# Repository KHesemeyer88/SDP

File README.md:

# SDP
Everyone has their own branch. 
You only work in your own branch.
Main only gets updated once a week and requires approval.
To collaborate in between, merge with your collaborator's branch back and forth.
To change branches: git checkout main, git checkout origin/YourBranch, etc.
To merge changes your collaborator made: git merge origin/CollaboratorBranch, etc.
  -Then resolve any merge conflicts, sync changes.

To get yourself up to date with main:
  -git checkout main
  -git pull
  -git checkout origin/YourBranch
  -git merge main

To merge person A to person B
-person A has updates / new code

In old/out_of_date branch

git merge the_branch_with_updates

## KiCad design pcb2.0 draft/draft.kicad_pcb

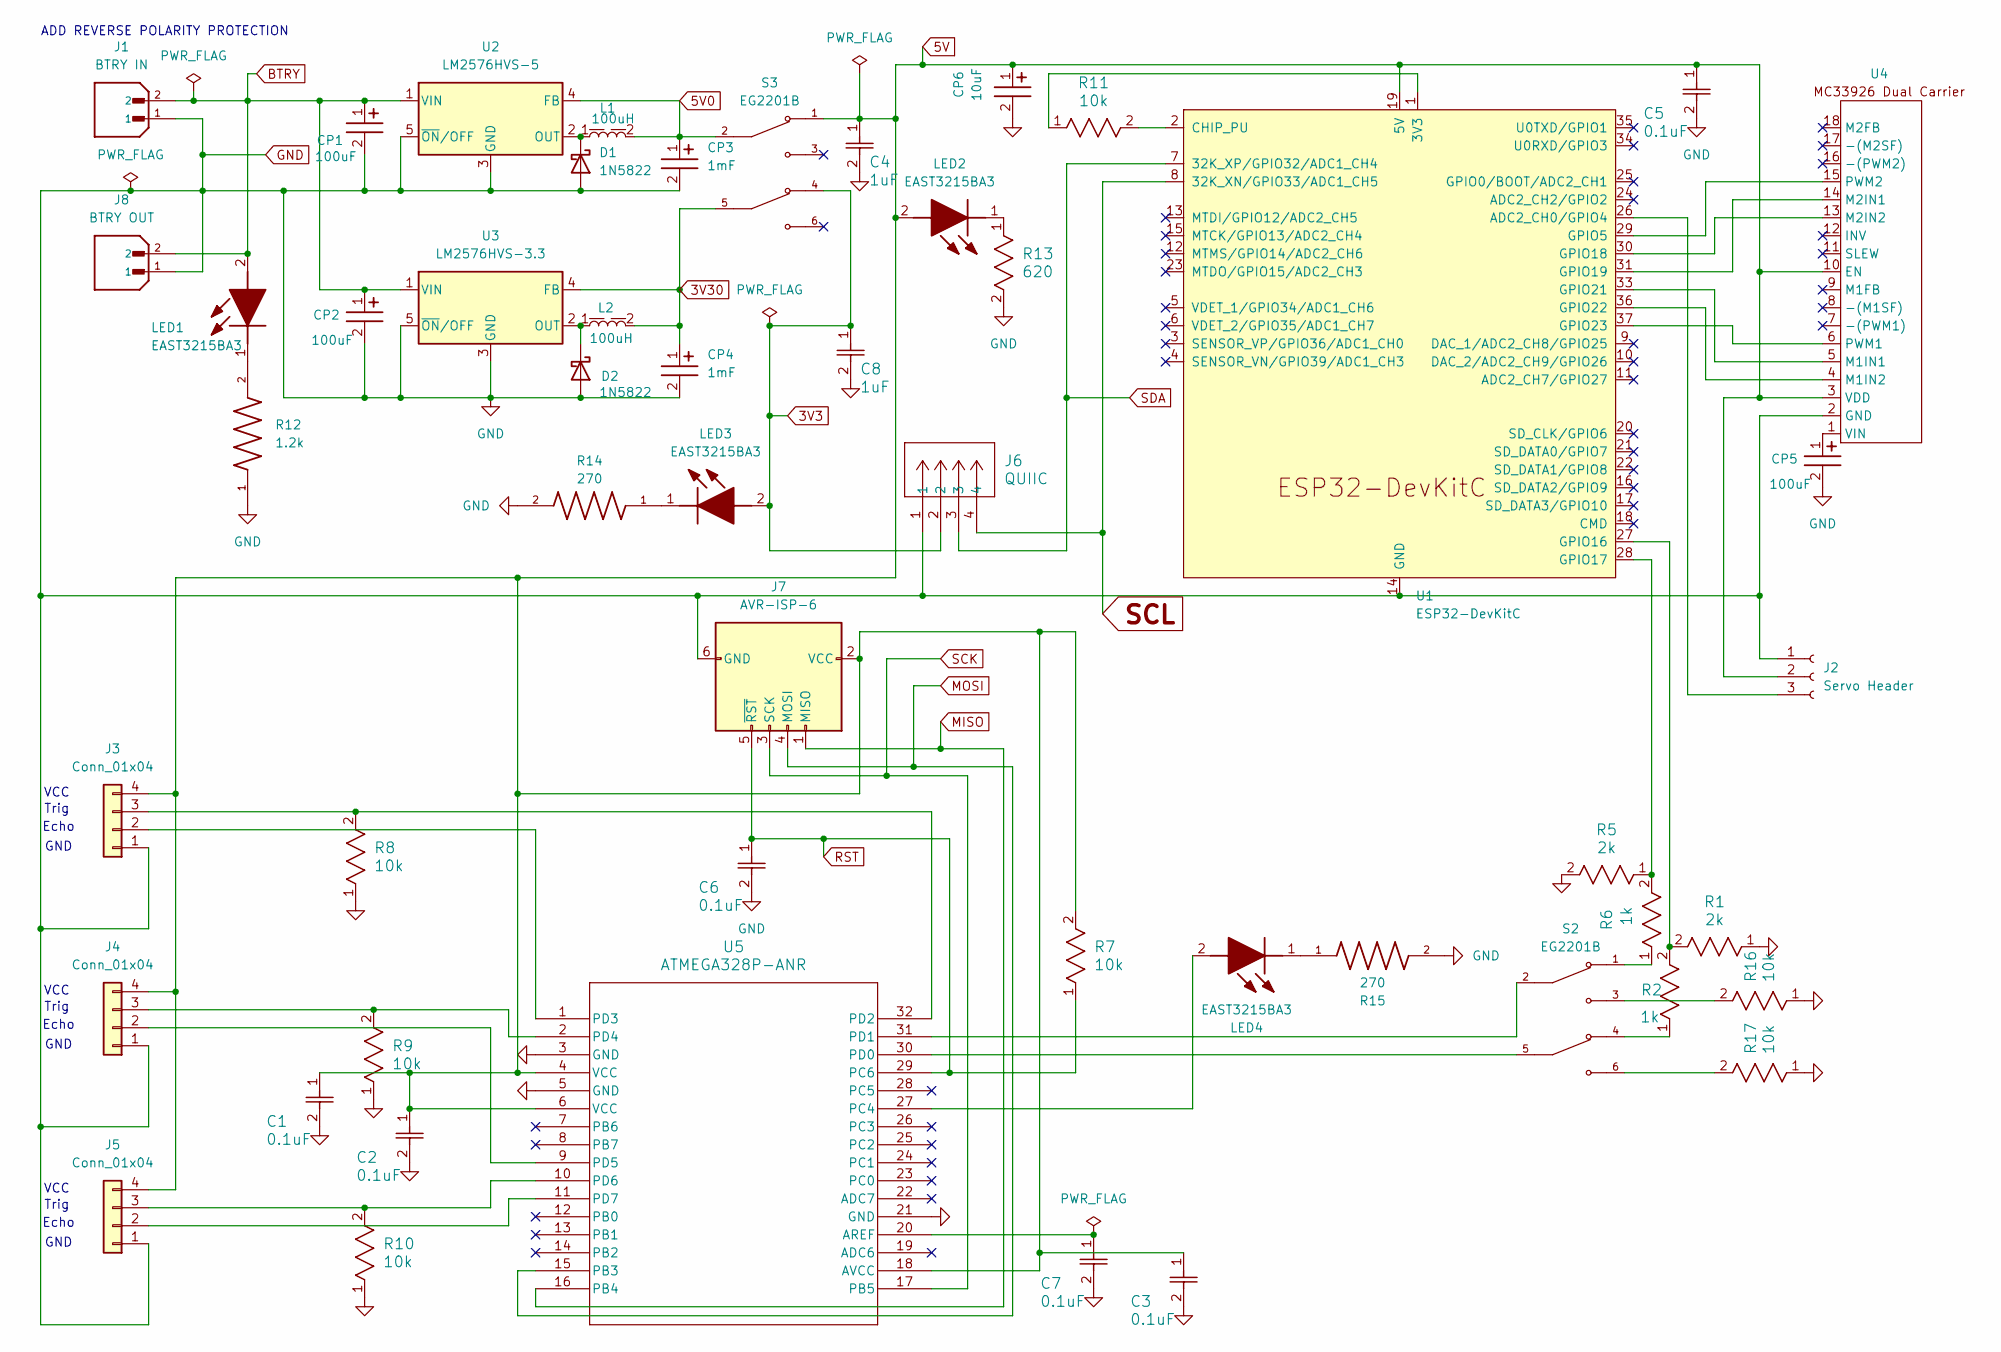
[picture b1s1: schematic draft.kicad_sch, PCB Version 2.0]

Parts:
C1, C2, C3, C5, C6, C7: 0.1uF; G-188_MUR-L
C4, C8: 1uF; CAP_GRM21_MUR-L
CP1, CP2, CP5: 100uF; CP_Wurth_WCAP-PSLP-D5L5.5; Part Number 875105242010
CP3, CP4: 1mF; CP_Wurth_WCAP-ASLI-D12.5L14; Part Number 865080462016
CP6: 10uF; CP_Wurth_WCAP-PSLP-D5L5.8; Part Number 875105359001
D1, D2: 1N5822; D_DO-201AD_P15.24mm_Horizontal
J1: BTRY IN; JST_B2B-XH-A; PARTREV N/A
J2: Servo Header; PinSocket_1x03_P2.54mm_Vertical
J3, J4, J5: Conn_01x04; PinHeader_1x04_P2.54mm_Vertical
J6: QUIIC; CONN_SM04B-SRSS-TB_JST
J7: AVR-ISP-6; IDC-Header_2x03_P2.54mm_Vertical
J8: BTRY OUT; JST_B2B-XH-A; PARTREV N/A
L1, L2: 100uH; L_Wurth_WE-PD-1245; Part Number 7447715101
LED1, LED2, LED3, LED4: EAST3215BA3; LEDC3215X110N; Mouser Part Number 638-EAST3215BA3
R1, R5: 2k; RES_CR0805_VEN-L
R2, R6: 1k; RES_CR0805_VEN-L
R7, R8, R9, R10, R11, R16, R17: 10k; RES_CR0805_VEN-L
R12: 1.2k; RES_ERJU08J122V; PARTREV 3/1/2020
R13: 620; RC1206N_PAN-L
R14, R15: 270; RES_ERJU08J271V; PARTREV 3/1/2020
S2, S3: EG2201B; SW_EG2201B; PARTREV C
U1: ESP32-DevKitC
U2: LM2576HVS-5; TO-263-5_TabPin3
U3: LM2576HVS-3.3; TO-263-5_TabPin3
U4: polulu_MC33926_dual
U5: ATMEGA328P-ANR; 32A_ATM-L

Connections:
3V3: C8.1, J6.2, LED3.2 (A), S3.4
3V30: CP4.1, L2.2, S3.5, U3.4 (FB)
5V: C1.1, C2.1, C3.1, C4.1, C5.1, CP6.1, J2.2, J3.4, J4.4, J5.4, J7.2 (VCC), LED2.2 (A), R7.2, S3.1, U1.19 (5V), U4.3 (VDD), U4.10 (EN), U5.4 (VCC), U5.6 (VCC), U5.18 (AVCC)
5V0: CP3.1, L1.2, S3.2, U2.4 (FB)
BTRY: CP1.1, CP2.1, J1.2, J8.2, LED1.2 (A), U2.1 (VIN), U3.1 (VIN)
GND: C1.2, C2.2, C3.2, C4.2, C5.2, C6.2, C7.2, C8.2, CP1.2, CP2.2, CP3.2, CP4.2, CP5.2, CP6.2, D1.2 (A), D2.2 (A), J1.1, J2.1, J3.1, J4.1, J5.1, J6.1, J7.6 (GND), J8.1, R1.1, R5.2, R8.1, R9.1, R10.1, R12.1, R13.2, R14.2, R15.2, R16.1, R17.1, U1.14 (GND), U1.32 (GND), U1.38 (GND), U2.3 (GND), U2.5 (~ON/OFF), U3.3 (GND), U3.5 (~ON/OFF), U4.2 (GND), U5.3 (GND), U5.5 (GND), U5.21 (GND)
MISO: J7.1 (MISO), U5.16 (PB4)
MOSI: J7.4 (MOSI), U5.15 (PB3)
unnamed: D1.1 (K), L1.1, U2.2 (OUT)
unnamed: D2.1 (K), L2.1, U3.2 (OUT)
unnamed: J2.3, U1.26 (ADC2_CH0/GPIO4)
unnamed: J3.2, U5.1 (PD3)
unnamed: J3.3, R8.2, U5.32 (PD2)
unnamed: J4.2, U5.9 (PD5)
unnamed: J4.3, R9.2, U5.2 (PD4)
unnamed: J5.2, U5.11 (PD7)
unnamed: J5.3, R10.2, U5.10 (PD6)
unnamed: LED1.1 (K), R12.2
unnamed: LED2.1 (K), R13.1
unnamed: LED3.1 (K), R14.1
unnamed: LED4.2 (A), U5.27 (PC4)
unnamed: LED4.1 (K), R15.1
unnamed: R2.1, S2.4
unnamed: R6.1, S2.1
unnamed: R16.2, S2.3
unnamed: R17.2, S2.6
unnamed: R11.1, U1.1 (3V3)
unnamed: R11.2, U1.2 (CHIP_PU)
unnamed: U1.29 (GPIO5), U4.15 (PWM2)
unnamed: R1.2, R2.2, U1.27 (GPIO16)
unnamed: R5.1, R6.2, U1.28 (GPIO17)
unnamed: U1.30 (GPIO18), U4.13 (M2IN2)
unnamed: U1.31 (GPIO19), U4.14 (M2IN1)
unnamed: U1.33 (GPIO21), U4.5 (M1IN1)
unnamed: U1.36 (GPIO22), U4.4 (M1IN2)
unnamed: U1.37 (GPIO23), U4.6 (PWM1)
unnamed: CP5.1, U4.1 (VIN)
unnamed: C7.1, U5.20 (AREF)
unnamed: S2.5, U5.30 (PD0)
unnamed: S2.2, U5.31 (PD1)
RST: C6.1, J7.5 (~RST), R7.1, U5.29 (PC6)
SCK: J7.3 (SCK), U5.17 (PB5)
SCL: J6.4, U1.8 (32K_XN/GPIO33/ADC1_CH5)
SDA: J6.3, U1.7 (32K_XP/GPIO32/ADC1_CH4)

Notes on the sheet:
GND
Echo
VCC
Trig
ADD REVERSE POLARITY PROTECTION

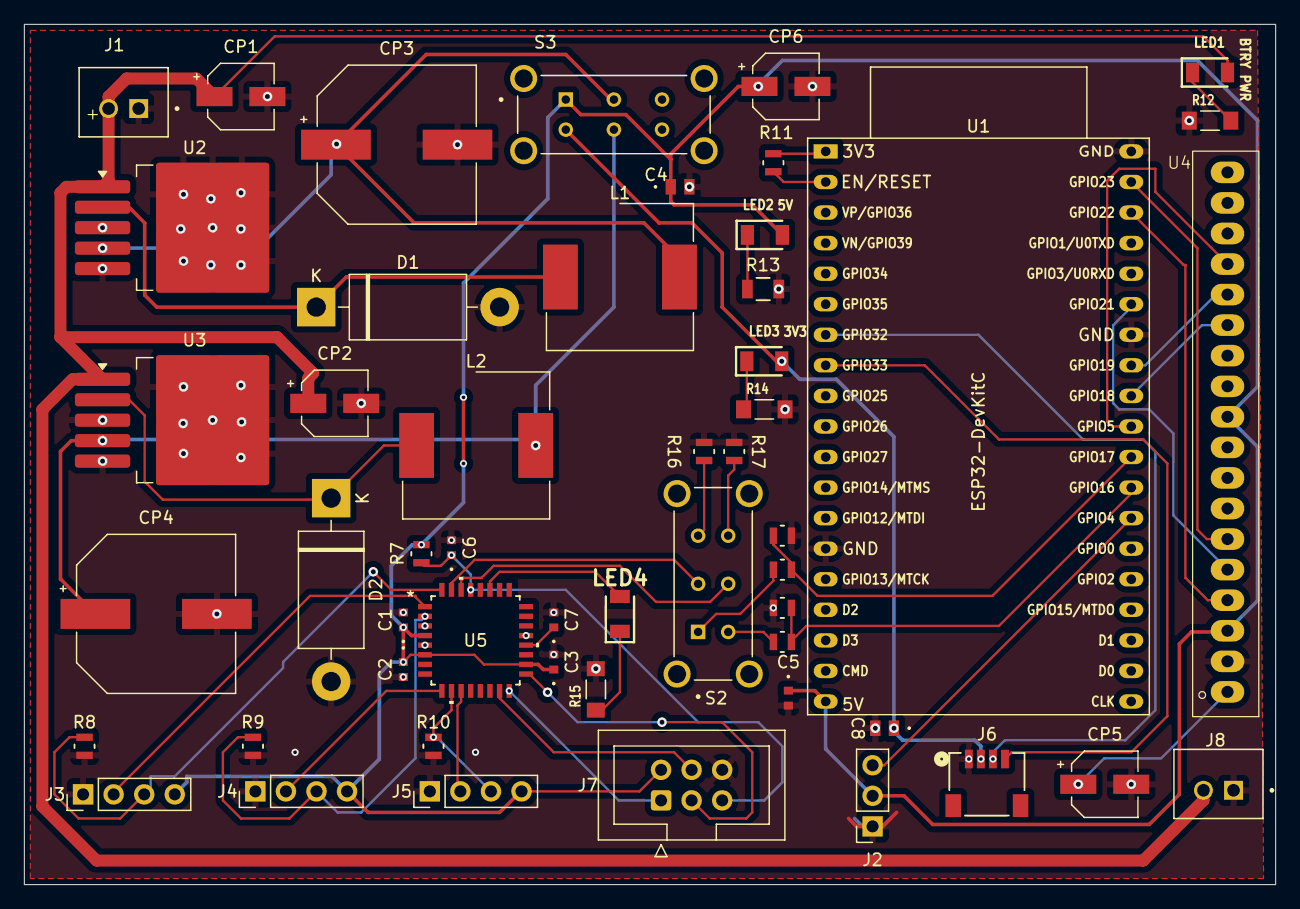
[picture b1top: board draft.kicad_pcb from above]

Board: 2 copper layers, 104.0 x 71.5 mm, 52 parts (0 on the bottom side), 44 nets.

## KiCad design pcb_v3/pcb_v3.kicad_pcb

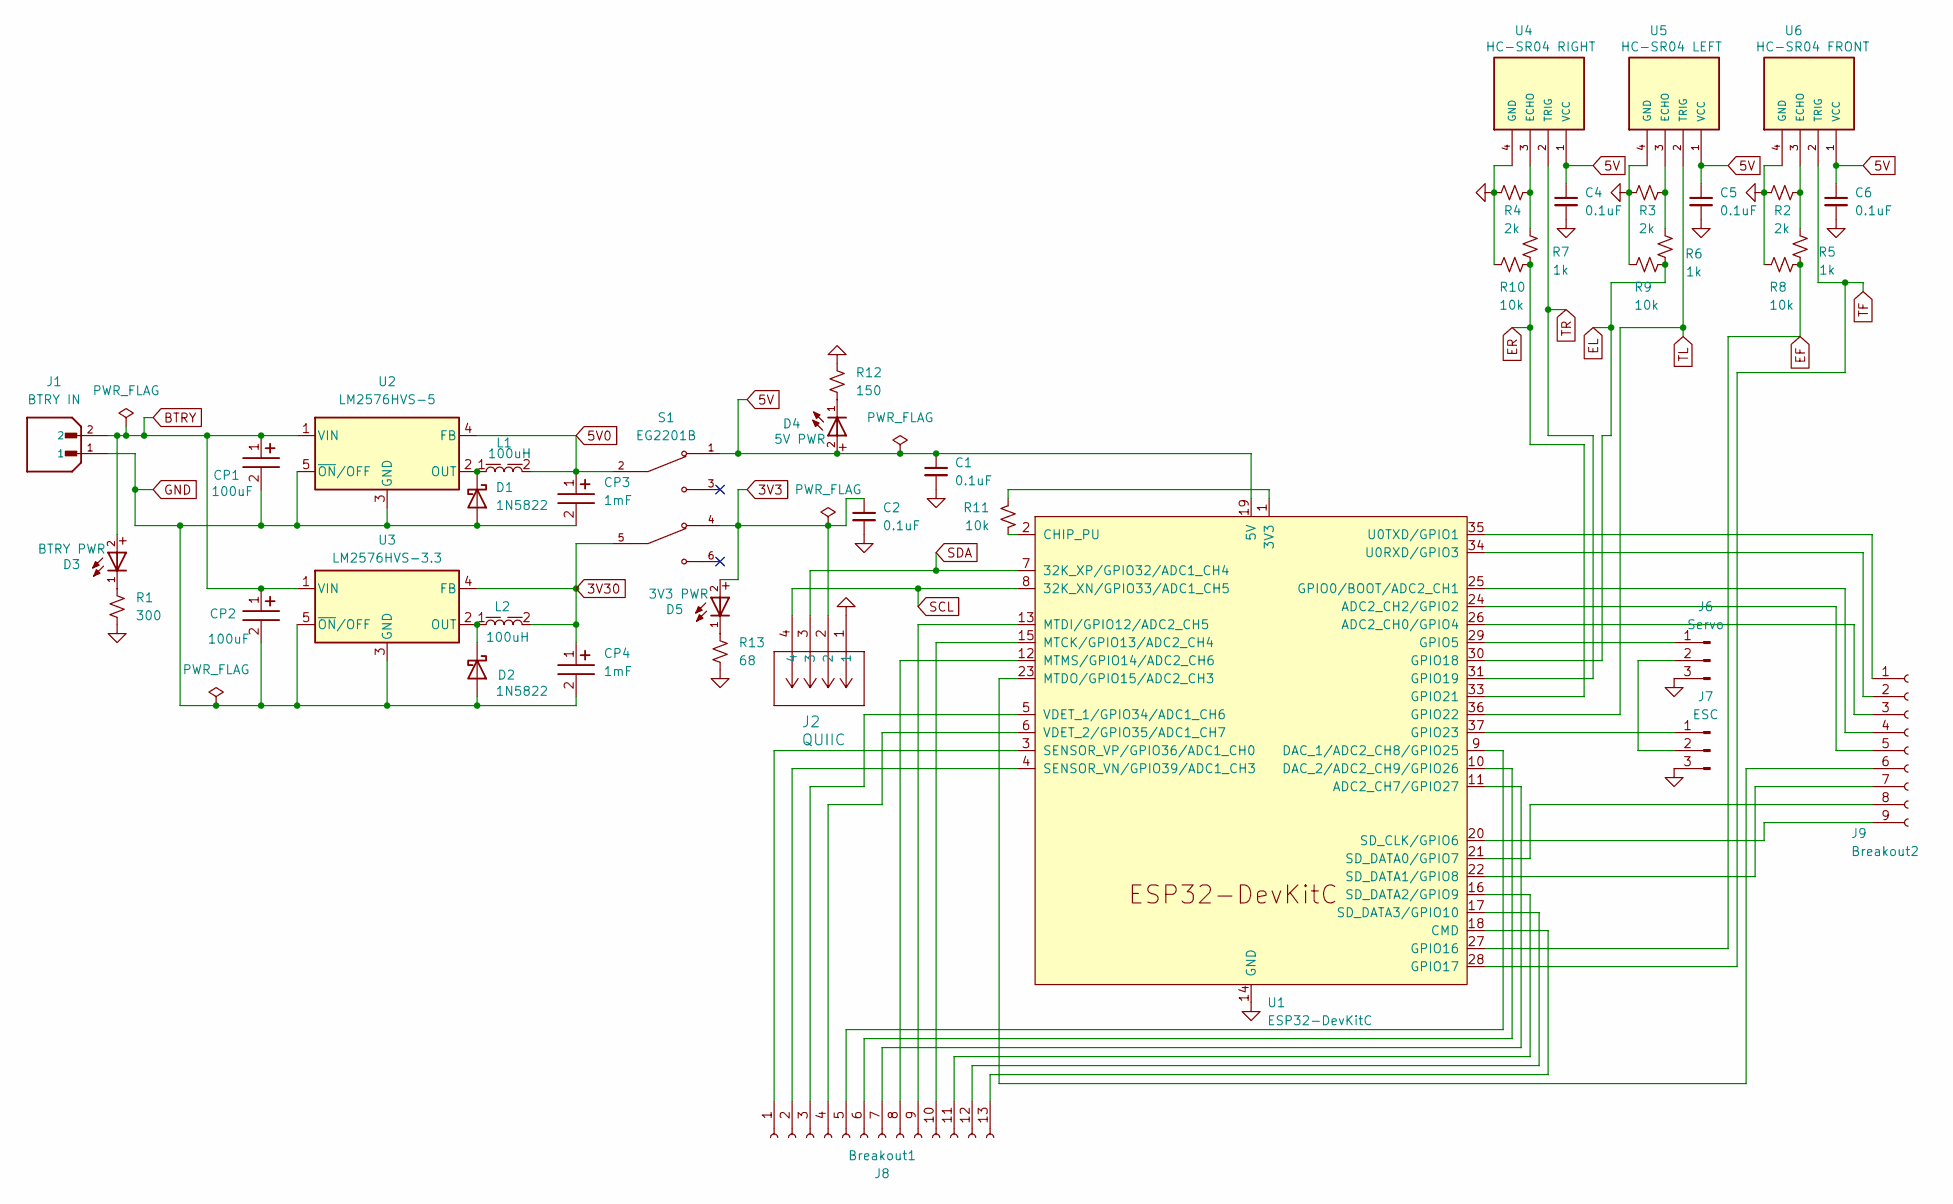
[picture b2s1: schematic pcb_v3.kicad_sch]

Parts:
C1, C2, C4, C5, C6: 0.1uF; C_1206_3216Metric_Pad1.33x1.80mm_HandSolder
CP1, CP2: 100uF; CP_Wurth_WCAP-PSLP-D5L5.5; Part Number 875105242010
CP3, CP4: 1mF; CP_Wurth_WCAP-ASLI-D12.5L14; Part Number 865080462016
D1, D2: 1N5822; D_DO-201AD_P15.24mm_Horizontal
D3: BTRY PWR; WL-SMSW_3014_LED
D4: 5V PWR; WL-SMSW_3014_LED
D5: 3V3 PWR; WL-SMSW_3014_LED
J1: BTRY IN; JST_B2B-XH-A; PARTREV N/A
J2: QUIIC; CONN_SM04B-SRSS-TB_JST
J6: Servo; JST_XH_B3B-XH-A_1x03_P2.50mm_Vertical
J7: ESC; JST_XH_B3B-XH-A_1x03_P2.50mm_Vertical
J8: Breakout1; PinSocket_1x13_P2.54mm_Vertical
J9: Breakout2; PinSocket_1x09_P2.54mm_Vertical
L1, L2: 100uH; L_Wurth_WE-PD-1245; Part Number 7447715101
R1: 300; R_1206_3216Metric_Pad1.30x1.75mm_HandSolder
R2, R3, R4: 2k; R_1206_3216Metric_Pad1.30x1.75mm_HandSolder
R5, R6, R7: 1k; R_1206_3216Metric_Pad1.30x1.75mm_HandSolder
R8, R9, R10, R11: 10k; R_1206_3216Metric_Pad1.30x1.75mm_HandSolder
R12: 150; R_1206_3216Metric_Pad1.30x1.75mm_HandSolder
R13: 68; R_1206_3216Metric_Pad1.30x1.75mm_HandSolder
S1: EG2201B; SW_EG2201B; PARTREV C
U1: ESP32-DevKitC
U2: LM2576HVS-5; TO-263-5_TabPin3
U3: LM2576HVS-3.3; TO-263-5_TabPin3
U4: HC-SR04 RIGHT; XCVR_HC-SR04
U5: HC-SR04 LEFT; XCVR_HC-SR04
U6: HC-SR04 FRONT; XCVR_HC-SR04

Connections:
3V3: C2.1, D5.2, J2.2, S1.4
3V30: CP4.1, L2.2, S1.5, U3.4 (FB)
5V: C1.1, C4.1, C5.1, C6.1, D4.2, S1.1, U1.19 (5V), U4.1 (VCC), U5.1 (VCC), U6.1 (VCC)
5V0: CP3.1, L1.2, S1.2, U2.4 (FB)
BTRY: CP1.1, CP2.1, D3.2, J1.2, U2.1 (VIN), U3.1 (VIN)
EF: R5.2, R8.1, U1.27 (GPIO16)
EL: R6.2, R9.1, U1.30 (GPIO18)
ER: R7.2, R10.1, U1.33 (GPIO21)
GND: C1.2, C2.2, C4.2, C5.2, C6.2, CP1.2, CP2.2, CP3.2, CP4.2, D1.2 (A), D2.2 (A), J1.1, J2.1, J6.3, J7.3, R1.2, R2.2, R3.2, R4.2, R8.2, R9.2, R10.2, R12.2, R13.2, U1.14 (GND), U1.32 (GND), U1.38 (GND), U2.3 (GND), U2.5 (~ON/OFF), U3.3 (GND), U3.5 (~ON/OFF), U4.4 (GND), U5.4 (GND), U6.4 (GND)
unnamed: D1.1 (K), L1.1, U2.2 (OUT)
unnamed: D2.1 (K), L2.1, U3.2 (OUT)
unnamed: D3.1, R1.1
unnamed: D4.1, R12.1
unnamed: D5.1, R13.1
unnamed: J6.1, U1.29 (GPIO5)
unnamed: J6.2, J7.2
unnamed: J7.1, U1.37 (GPIO23)
unnamed: J8.1, U1.3 (SENSOR_VP/GPIO36/ADC1_CH0)
unnamed: J8.2, U1.4 (SENSOR_VN/GPIO39/ADC1_CH3)
unnamed: J8.3, U1.5 (VDET_1/GPIO34/ADC1_CH6)
unnamed: J8.4, U1.6 (VDET_2/GPIO35/ADC1_CH7)
unnamed: J8.5, U1.9 (DAC_1/ADC2_CH8/GPIO25)
unnamed: J8.6, U1.10 (DAC_2/ADC2_CH9/GPIO26)
unnamed: J8.7, U1.11 (ADC2_CH7/GPIO27)
unnamed: J8.8, U1.12 (MTMS/GPIO14/ADC2_CH6)
unnamed: J8.9, U1.13 (MTDI/GPIO12/ADC2_CH5)
unnamed: J8.10, U1.15 (MTCK/GPIO13/ADC2_CH4)
unnamed: J8.11, U1.16 (SD_DATA2/GPIO9)
unnamed: J8.12, U1.17 (SD_DATA3/GPIO10)
unnamed: J8.13, U1.18 (CMD)
unnamed: J9.1, U1.35 (U0TXD/GPIO1)
unnamed: J9.2, U1.34 (U0RXD/GPIO3)
unnamed: J9.3, U1.26 (ADC2_CH0/GPIO4)
unnamed: J9.4, U1.25 (GPIO0/BOOT/ADC2_CH1)
unnamed: J9.5, U1.24 (ADC2_CH2/GPIO2)
unnamed: J9.6, U1.23 (MTDO/GPIO15/ADC2_CH3)
unnamed: J9.7, U1.22 (SD_DATA1/GPIO8)
unnamed: J9.8, U1.21 (SD_DATA0/GPIO7)
unnamed: J9.9, U1.20 (SD_CLK/GPIO6)
unnamed: R11.1, U1.1 (3V3)
unnamed: R11.2, U1.2 (CHIP_PU)
unnamed: R4.1, R7.1, U4.3 (ECHO)
unnamed: R3.1, R6.1, U5.3 (ECHO)
unnamed: R2.1, R5.1, U6.3 (ECHO)
SCL: J2.4, U1.8 (32K_XN/GPIO33/ADC1_CH5)
SDA: J2.3, U1.7 (32K_XP/GPIO32/ADC1_CH4)
TF: U1.28 (GPIO17), U6.2 (TRIG)
TL: U1.36 (GPIO22), U5.2 (TRIG)
TR: U1.31 (GPIO19), U4.2 (TRIG)

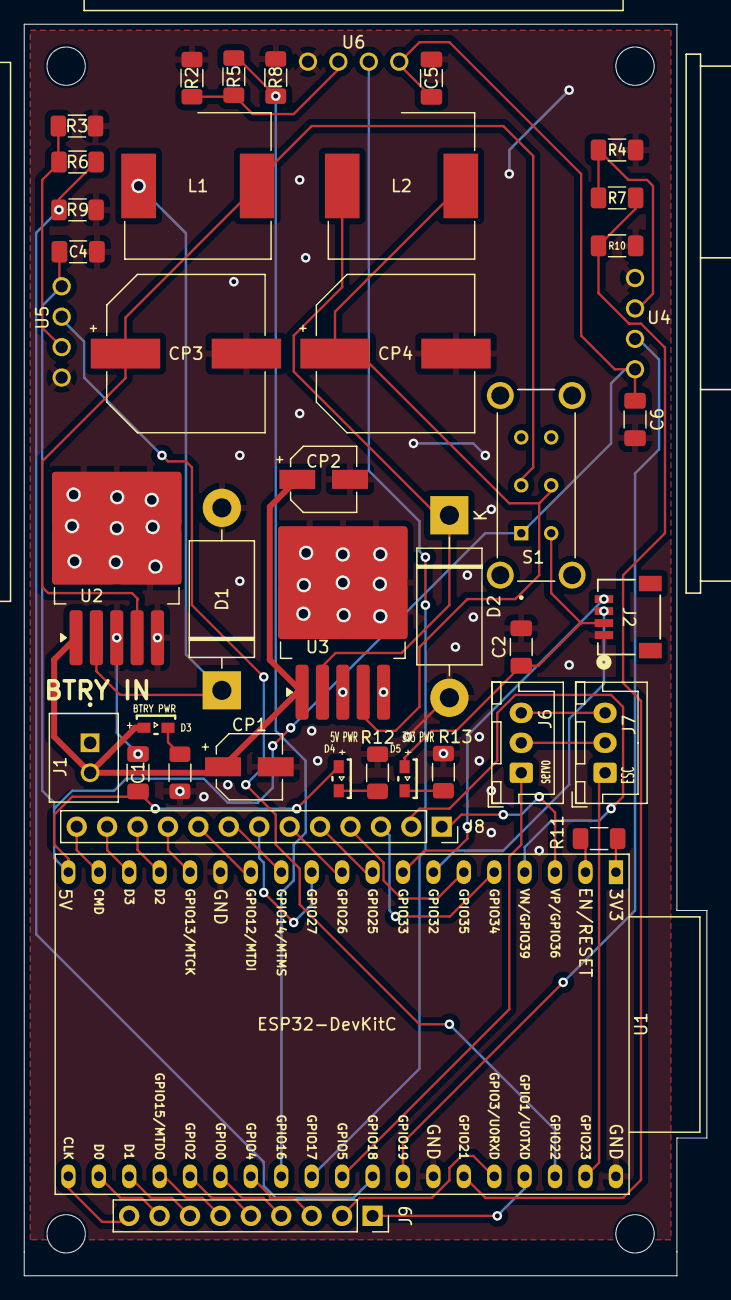
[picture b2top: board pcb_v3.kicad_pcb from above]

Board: 2 copper layers, 57.0 x 104.5 mm, 42 parts (0 on the bottom side), 49 nets.

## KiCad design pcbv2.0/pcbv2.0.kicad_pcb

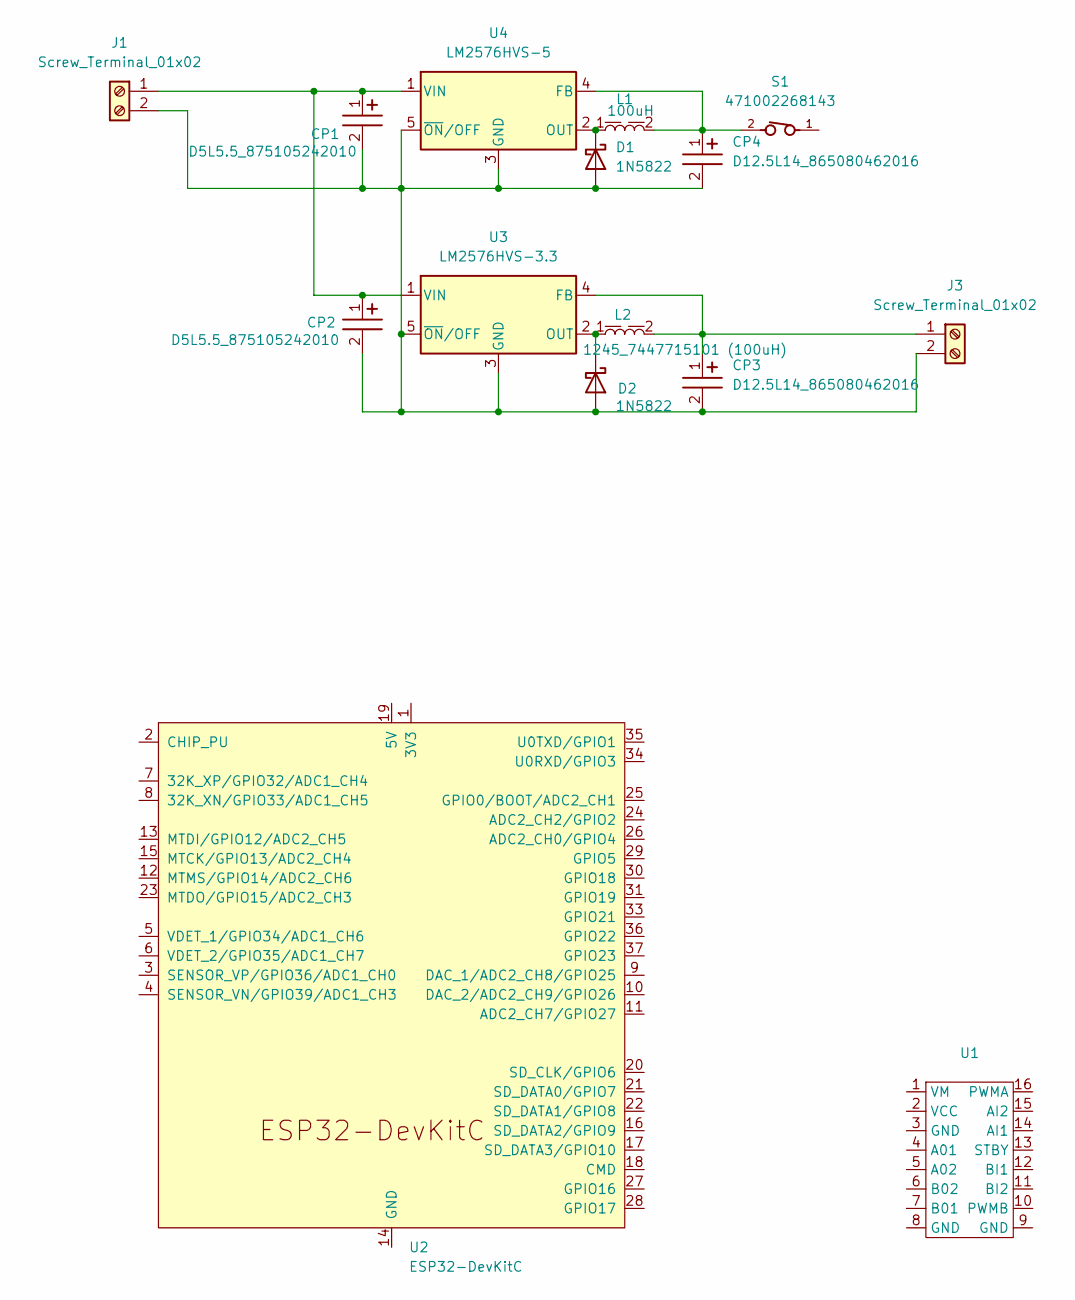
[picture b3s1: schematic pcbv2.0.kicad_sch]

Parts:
CP1, CP2: D5L5.5_875105242010; CP_Wurth_WCAP-PSLP-D5L5.5; Part Number 875105242010
CP3, CP4: D12.5L14_865080462016; CP_Wurth_WCAP-ASLI-D12.5L14; Part Number 865080462016
D1, D2: 1N5822; D_DO-201AD_P15.24mm_Horizontal
J1, J3: Screw_Terminal_01x02; CUI_TB002-500-02BE
L1: 100uH; L_Wurth_WE-PD-1245; Part Number 7447715101
L2: 1245_7447715101 (100uH); L_Wurth_WE-PD-1245; Part Number 7447715101
S1: 471002268143; switch_471002268143_actual; PART-NUMBER 471002268143
U1: TB6612FNG_BoB
U2: ESP32-DevKitC
U3: LM2576HVS-3.3; TO-263-5_TabPin3
U4: LM2576HVS-5; TO-263-5_TabPin3

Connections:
unnamed: CP1.2, CP2.2, CP3.2, CP4.2, D1.2 (A), D2.2 (A), J1.2, J3.2, U3.3 (GND), U3.5 (~ON/OFF), U4.3 (GND), U4.5 (~ON/OFF)
unnamed: D1.1 (K), L1.1, U4.2 (OUT)
unnamed: D2.1 (K), L2.1, U3.2 (OUT)
unnamed: CP1.1, CP2.1, J1.1, U3.1 (VIN), U4.1 (VIN)
unnamed: CP3.1, J3.1, L2.2, U3.4 (FB)
unnamed: U2.14 (GND), U2.32 (GND), U2.38 (GND)
unnamed: CP4.1, L1.2, S1.2, U4.4 (FB)

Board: 2 copper layers, 15 parts (0 on the bottom side), 7 nets, no tracks yet.

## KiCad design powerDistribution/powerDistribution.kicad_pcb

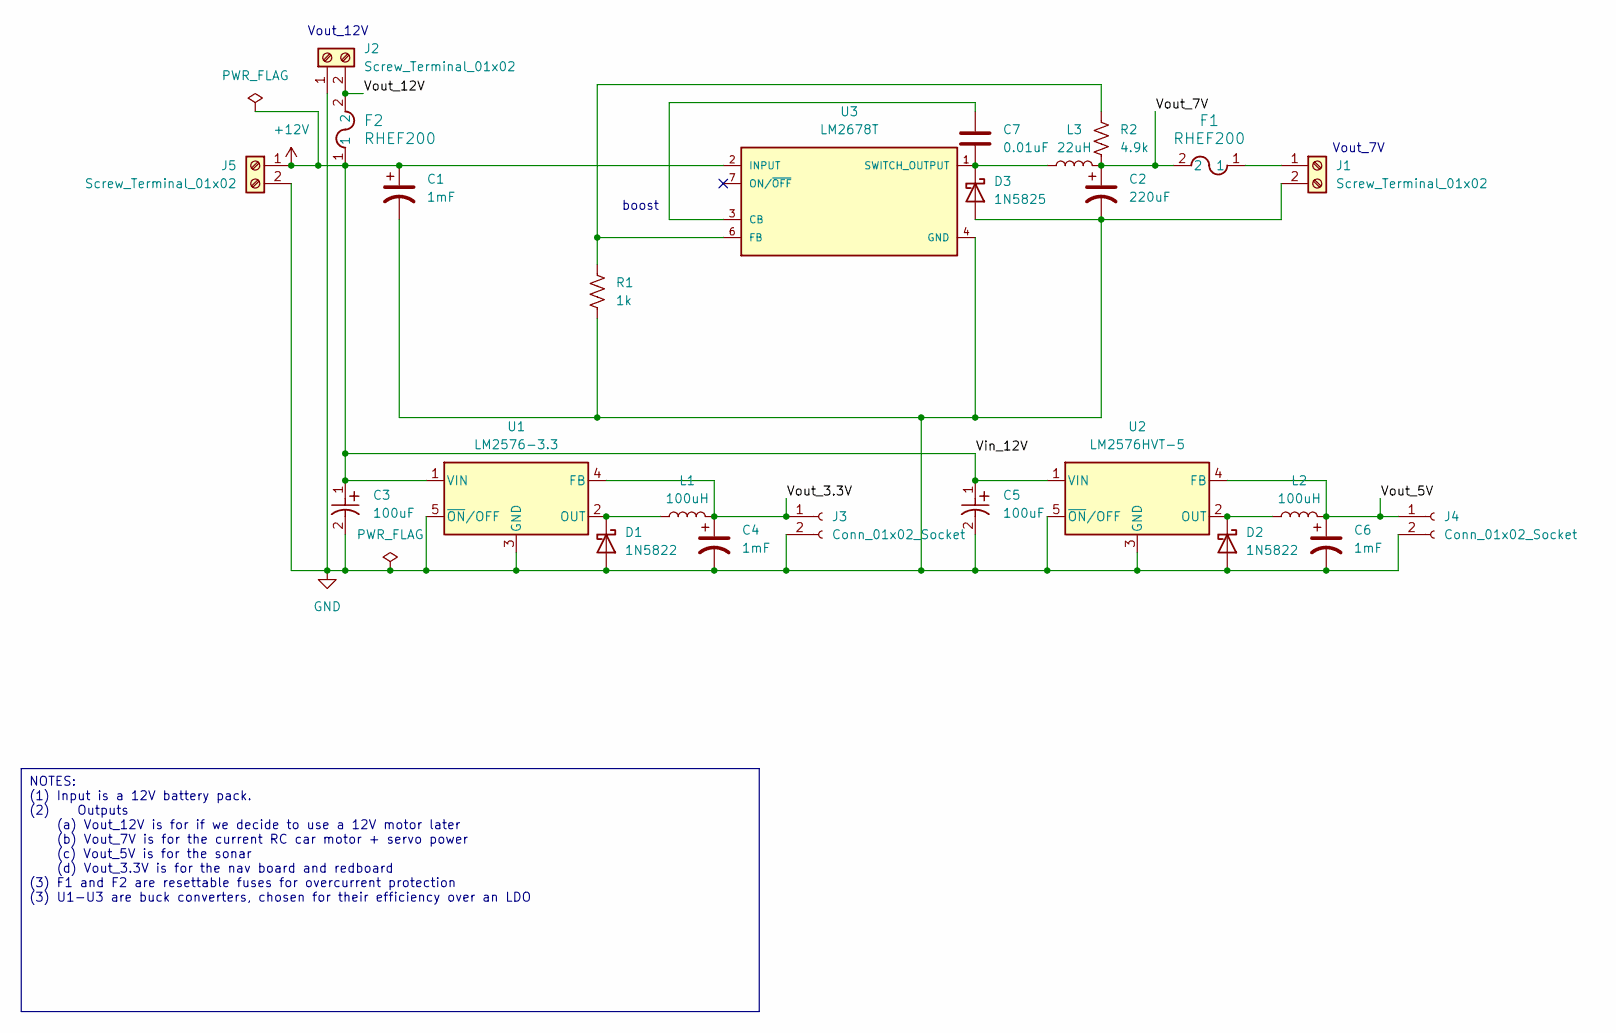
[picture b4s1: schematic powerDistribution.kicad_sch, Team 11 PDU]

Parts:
C1, C4, C6: 1mF; CAP_12.5 X 25_NCH
C2: 220uF; PCAP_10x16-THRU-ELECT_NCA
C3, C5: 100uF; PCAP_10x16-THRU-ELECT_NCA
C7: 0.01uF; PHE-BD_KEM
D1, D2: 1N5822; D_DO-201AD_P12.70mm_Horizontal
D3: 1N5825; D_DO-201AD_P12.70mm_Horizontal
F1, F2: RHEF200; FUS_RHEF100_TYCO_TYC
J1, J2, J5: Screw_Terminal_01x02; CUI_TB002-500-02BE
J3, J4: Conn_01x02_Socket; CONN_PPPC021_SUL
L1, L2: 100uH; 1410454C_MUR
L3: 22uH; 1422311C_MUR
R1: 1k; STA_RNF14_STP
R2: 4.9k; STA_RNF14_STP
U1: LM2576-3.3; T05A_TEX
U2: LM2576HVT-5; T05A_TEX
U3: LM2678T; TO127P1041X469X2199-7N

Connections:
+12V: C1.1, C3.1, C5.1, F2.1, J5.1, U1.1 (VIN), U2.1 (VIN), U3.2 (INPUT)
/Vout_3.3V: C4.1, J3.1, L1.2, U1.4 (FB)
/Vout_5V: C6.1, J4.1, L2.2, U2.4 (FB)
/Vout_7V: C2.1, F1.2, L3.2, R2.2
/Vout_12V: F2.2, J2.2
GND: C1.2, C2.2, C3.2, C4.2, C5.2, C6.2, D1.2 (A), D2.2 (A), D3.2 (A), J1.2, J2.1, J3.2, J4.2, J5.2, R1.1, U1.3 (GND), U1.5 (~ON/OFF), U2.3 (GND), U2.5 (~ON/OFF), U3.4 (GND)
unnamed: D1.1 (K), L1.1, U1.2 (OUT)
unnamed: D2.1 (K), L2.1, U2.2 (OUT)
unnamed: C7.2, D3.1 (K), L3.1, U3.1 (SWITCH_OUTPUT)
unnamed: F1.1, J1.1
unnamed: C7.1, U3.3 (CB)
unnamed: R1.2, R2.1, U3.6 (FB)

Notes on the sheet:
NOTES: (1) Input is a 12V battery pack. (2) Outputs (a) Vout_12V is for if we decide to use a 12V motor later (b) Vout_7V is for the current RC car motor + servo power (c) Vout_5V is for the sonar (d) Vout_3.3V is for the nav board and redboard (3) F1 and F2 are resettable fuses for overcurrent pro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
Vout_12V
boost
Vout_7V

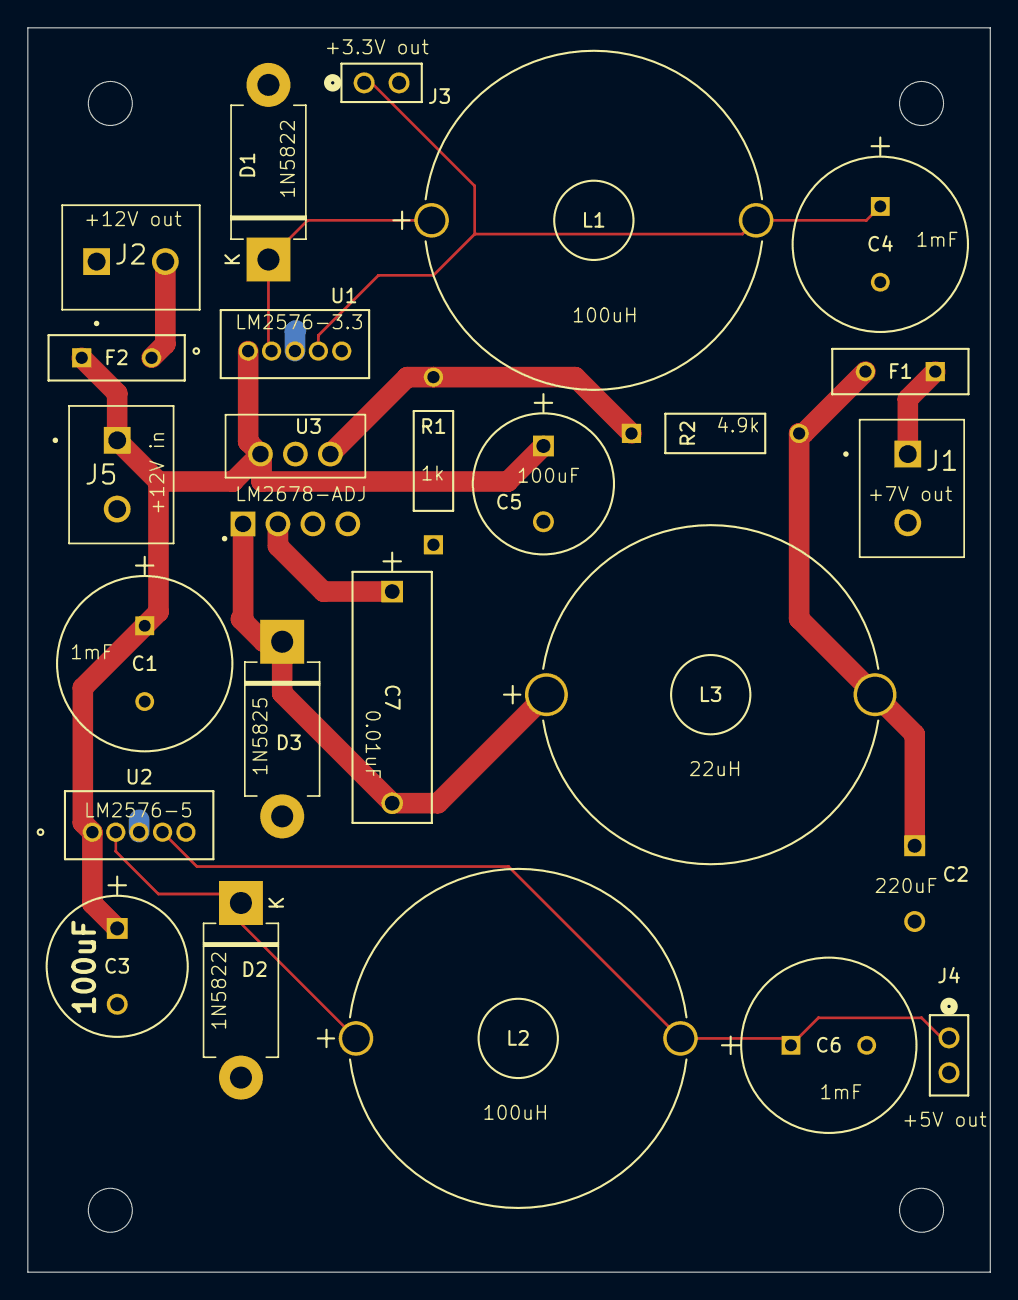
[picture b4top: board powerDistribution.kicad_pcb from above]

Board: 2 copper layers, 70.0 x 90.5 mm, 25 parts (1 on the bottom side), 12 nets.

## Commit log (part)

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2024-06-28 initial test commit message
2024-06-28 Adding cloing instructions
2024-11-06 Add power distribution board KiCad project files
2024-11-18 Removing junk files
2024-12-02 Adding pacer_car_main
2024-12-02 current gnss position and heading txt file
2024-12-02 read arduino serial of current gnss reading
2024-12-03 Reading from gnss and getting distance to next waypoint
2024-12-03 fixed right turn_angle
2024-12-03 Ignore import serial error
2025-02-05 brent's wifi_test_6
2025-02-05 MDR stuff
2025-02-05 for real this time
2025-02-05 stuff
2025-02-05 wifi_test_7
2025-02-09 sync
2025-02-10 completed draft of pcbv2 - in "draft" folder
2025-02-10 forgot to unignore folder
2025-02-10 some more schematic updates
2025-02-11 completed pcb layout
2025-02-12 autonomous ctrl v1
2025-02-12 nav v2
2025-02-17 added basic sonar (works but needs work)
2025-02-22 pcb version 3 complete
2025-02-23 multi-waypoint nagivation added
2025-02-24 fixed sonar latching issue
2025-02-27 Latest - add state machine
2025-02-28 broke out code into header files
2025-02-28 created archive folder
2025-02-28 1st attempt at looping waypoints, pace
2025-02-28 UI improvements, rough time/distance/pace tracking
2025-02-28 fixed psychotic pace behavior (hopefully)
2025-02-28 unbroke everything
2025-02-28 seriously, fixed broken stuff
2025-03-01 simpler pace control, still choppy
2025-03-01 Added next steps comments in main .ino file
2025-03-01 Added comment: NEED AUTO TIMEOUT
2025-03-04 Updated traxxas_v2.ino
2025-03-04 updated pace control
2025-03-04 updated distance&time tracking
2025-03-04 still need works
2025-03-05 extra comments
2025-03-05 Timing improvements, global safety timeout fixed
2025-03-05 Stella clean
2025-03-05 dumb file removed
2025-03-05 test
2025-03-05 combined mine and Stella's work
2025-03-06 test v20
2025-03-06 text v21
2025-03-06 ultra test
2025-03-06 fuck
2025-03-06 Update README.md again
2025-03-07 implemented callbacks, P-I pace control
2025-03-09 emergy avoidance in manual mode
2025-03-09 Update traxxas_v2.ino - without emergency avoidance
2025-03-09 deleted extra files
2025-03-09 clean & workingish initial thing
2025-03-10 it wooooorks, kinda? pretty good
2025-03-10 Fixed stright line phase, improved pace ctrl
2025-03-10 intergrating RTK to main?
2025-03-10 some rtk stuff
2025-03-11 first attempt, wants the wall
2025-03-11 added comments
2025-03-12 Save my latest changes to traxxas_v2.ino
2025-03-12 Working RTK on car!
2025-03-12 halfway to websocket implementation
2025-03-13 synchronous websockets implemented, seems to work
2025-03-13 cleaned up legacy webhandlers
2025-03-14 first attempt at lidar, page not loading
2025-03-15 lidar working
2025-03-15 improved manual mode responsiveness, still bad tho
2025-03-15 final changes pre-FreeRTOS attempt
2025-03-15 made lidar code much faster
2025-03-16 added microsd setup and waypoint logging
2025-03-17 hello world with freeRTOS
2025-03-17 basic manual mode implemented and working
2025-03-19 Cleaned up disastrous file structure
2025-03-19 updated gitignore
2025-03-19 Clean PlatformIO structure without FreeRTOS directories
2025-03-20 implemented debug logging to sd, added GNSS/RTK reporting
2025-03-20 Enhanced logging, added system time update from GNSS
2025-03-20 first attempt at full auto nav in freertos
2025-03-20 changed to async websocket libraries
2025-03-21 fixed manual reverse bug
2025-03-22 fixed system reset issue (don't use String!!!!!). Not yet field tested
2025-03-22 first successful field test with RTOS
2025-03-24 changed websocket priority
2025-03-24 massive cleanup - code not field tested
2025-03-25 restructured logging a bit, see analysis github repo
2025-03-26 updataed pin assignments in config for new board
2025-03-27 adjusted sendGPSData to only hold mutex long enough to grab data
2025-03-28 pin updates for nav SPI
2025-03-28 code currently broken, tried to implement SPI
2025-03-28 LOG_DEBUG baseline rework
2025-03-28 moved log file to its folder
2025-03-30 changed SPI pin assignment
2025-03-30 first attempt at complete SPI integration
2025-03-30 changed loglevel
2025-03-31 solved new reboot issue, working on getting SPI comms with nav board
2025-03-31 HOLY SHIT WORKING SPI
2025-03-31 tried to match baseline logging
2025-03-31 Resolved conflicts and updated files
2025-04-02 BY FAR BEST FIELD TEST TO DATE
2025-04-02 MAGS
2025-04-02 data.count || thing
2025-04-02 increased mutex efficiency of processGNSSConnection and renamed to processRTKConnection
2025-04-02 made connectToNTRIP more efficient, hopefully
2025-04-02 brought rtk status panel to manual page
2025-04-02 updated websocket_handler
2025-04-02 restored connectToNTRIP
2025-04-04 added logging for position LATENCY, changed task priorities
2025-04-04 brought in sparkfun GNSS library..........
2025-04-04 commented out _outputPort.write(incoming) and if (_outputPort != _ubxOutputPort) in sparkfun library. NOT tested, other than a successful build
2025-04-04 Refactored payloadAuto to use static buffer, removed heap allocation and deallocation
    - Replaced dynamically allocated payloadAuto with fixed-size array payloadAutoStatic[256]
    - Updated packetAuto to use static buffer instead of runtime allocation
    - Removed all new[]/delete[] logic related to payloadAuto
    - Eliminated payloadAutoBytes tracking
    - Ensures safer and more deterministic memory use under RTOS
    ---NOT TESTED, but successful build
2025-04-04 Disabled NMEA and RTCM parsing for UBX-only SPI mode
    - Added early-out in process() to ignore non-UBX bytes unless mid-sentence
    - Commented out NMEA and RTCM sentence-type detection logic
    - Disabled full NMEA and RTCM parsing branches using #if 0
    - Parser now handles UBX messages only, reducing CPU load and SPI overhead
    - Prepared system for cleaner real-time GNSS task timing
    ---NOT TESTED, but successful build
2025-04-04 Trim GNSS callback system to NAV-PVT only
    - Replaced checkCallbacks() with checkPVTCallbackOnly() to reduce per-cycle callback overhead
    - Avoided unnecessary conditional checks for unused UBX message types
    - Retained original checkCallbacks() in codebase (commented out) for reference
    - Confirmed GGA and RTCM functionality not affected by UBX-only SPI output
    Expecting significant performance improvement in GNSS task timing
    ---NOT TESTED, but successful build
2025-04-04 Refactor RTCM injection: separate RTCMTask, ring buffer, and SPI mutex coordination
    - Created RTCMTask to isolate pushRawData() calls from GNSS task
    - Added ring buffer (4096 bytes) for asynchronous RTCM ingestion
    - GNSS task now writes RTCM to buffer instead of pushing directly
    - SPI bus access to myGPS is now mutex-protected (spiBusMutex)
    - RTCMTask drains buffer at fixed 2Hz using vTaskDelayUntil()
    - Improves modularity, SPI timing isolation, and logging clarity
2025-04-04 Refine RTCM buffering and logging: fix drop counting, add push timing diagnostics
    - Fixed droppedRtcmBytes accounting in writeRtcmData(): now only increments on actual overflow
    - Consolidated RTCM logging in RTCMTask(): buffer depth and drop count logged every 10 cycles
    - Added duration timing for pushRawData() in RTCMTask with correct format specifier (%lu)
    - Minor cleanup of variable scope and unnecessary statics in RTCMTask()
    - Improved logging clarity for diagnosing SPI injection timing and buffer behavior
    ---NOT TESTED, but successful build
2025-04-05 Add debug logging for analysis
2025-04-05 changed logs commented out a bit
2025-04-05 debug logging changed for comparison
2025-04-05 change debug logging for comparison
2025-04-06 first pass at bypassing sparkfun library; uploads but no GNSS or RTK activity
2025-04-06 still doesn't work
2025-04-06 no dice
2025-04-06 FIRST WORKING GNSS WITHOUT SPARKFUN. Still no RTK
2025-04-06 FIRST FULLY FUNCTIONAL RTK ENABLED!!!!!!!!!!!!!!!!!!!!
2025-04-06 various timing improvements, lost rtk
2025-04-07 pre-replacement of gnss.cpp. set/get commands not working
2025-04-07 mutex protected the gnss SPI bus
2025-04-07 no dice after changing val set and get functions
2025-04-07 argh
2025-04-07 tried to fix GGA generation, still no dice.
2025-04-07 RTK ACHIEVED FINALLY. NOTE THIS VERSION REQUIRES SETTINGS TO BE CONFIGURED IN U-BLOX
2025-04-07 Added logging. Major issues with controlTask, NavigationTask, and position-control latency time. pushRawData too high, but not the primary suspect.
2025-04-07 move nav task to core 0
2025-04-08 obstacle within 2m triggers avoidance
    slow speed and steering right/left (alternating)
2025-04-08 updated port (MacOS)
2025-04-08 Changed wait for mutex times from 5 to 50 for navData and GNSSData mutexes in NavigationTask. Not tested.
2025-04-08 added mutex timeout error messages in nav task and helper functions. Not tested.
2025-04-08 built shadow GNSS struct to cut down on GNSSData mutex contention. Not tested
2025-04-08 added nav update skip error log, not tested.
2025-04-09 Increased control task priority, decreased GNSS, increased navdatamutex wait time in control task, increased waypointmutex wait time in control task, increased servomutex wait time in control task. B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
2025-04-09 put nav task back on core 1
2025-04-09 Found major error, heading and speed were hardcoded to 0
2025-04-09 initial ws json to binary switch
2025-04-09 added wait for 50 0xFFs
2025-04-09 it lives / compile errors
2025-04-09 remove com port shit
2025-04-10 lost rtk in timing improvement attempts, need to fix. rewrote connecttontrip and processrtkconnection
2025-04-10 scrubbed logs. RTK float is back, timing is terrible
2025-04-11 stupid updateTarget vestige
2025-04-11 changed to colrain base station
2025-04-11 change core assignment, gga and gnss to 1 from 0
2025-04-11 added logging, put gnss task on core 0
2025-04-11 THIS IS THE BASE VERSION, WORKS AT 4.4m/s, 2m radius
2025-04-11 First attempt at PID library for throttle. Works well, but first startup is very slow.
2025-04-13 set standard mutexWait times
2025-04-14 fixed struct size
2025-04-14 WS STRUCTS WORK
2025-04-14 ahhhhhhhhhh
2025-04-14 decimal places
2025-04-16 This version works but steering seems wild, maybe becuase of weather?
2025-04-16 good steering control, good field test in quad
2025-04-16 successfully avoidance!
2025-04-16 added mutexWait
2025-04-18 This branch is in case we want lidar-free code for demo. Also using it to tune PID parameters, and MADE VERY IMPORTANT UPDATES TO GNSS, in initializeGNSS()
2025-04-21 dropped left/right obst from manual page, playing with PID params
2025-04-21 got rid of DYNMODEL assignment, bad results. This is perfect, other than pace control
2025-04-21 THE BEST OBSTACLE AVOIDANCE. Pace control is not going to work without anti-windup logic
2025-04-22 FPR CODE
2025-04-23 FPR CODE (FOR REAL THIS TIME)
2025-04-24 FPR CODE, BUT LIKE FOR SERIOUS THIS TIME
2025-04-24 IT FUCKING WORKSSSSSSSSSSSSSSSSSSSSSSSSSSSSSSSSSSSSSSSS
2025-04-24 FPR demo code
2025-04-30 fixing demo button
2025-05-02 too many messages, closing connection
2025-05-02 idk again
2025-05-02 log WP routes to SD card. Still having "too many messages queued: closing connection" always been there?
2025-05-02 route names from SD card sent to route selector dropdown. I swear that overload ws connection shit was here before, but I rewrite everything anyways...
    I need to be commiting more on each successful step
2025-05-02 removed marcus_tri image / user selecting route works?
2025-05-02 all messages are sent and start nav should work, hard coded pace and distance rn
2025-05-02 added pace and distance to route start. Getting brownout or smg (webpage not loading) when SD card is in
2025-05-02 add delay before sd.begin, no fix
2025-05-02 moved sd init after http begin, no fix
2025-05-02 added delay before sd init, after https init (which i should have done eariler) pretty sure that fixed it. Also added manual SD card reboot. Added marcus loop image back. Still some small webpage pro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
2025-05-02 small webpage fixes, start route not starting
2025-05-02 car now starts on route start press
2025-05-02 generic hotspot for demo day
